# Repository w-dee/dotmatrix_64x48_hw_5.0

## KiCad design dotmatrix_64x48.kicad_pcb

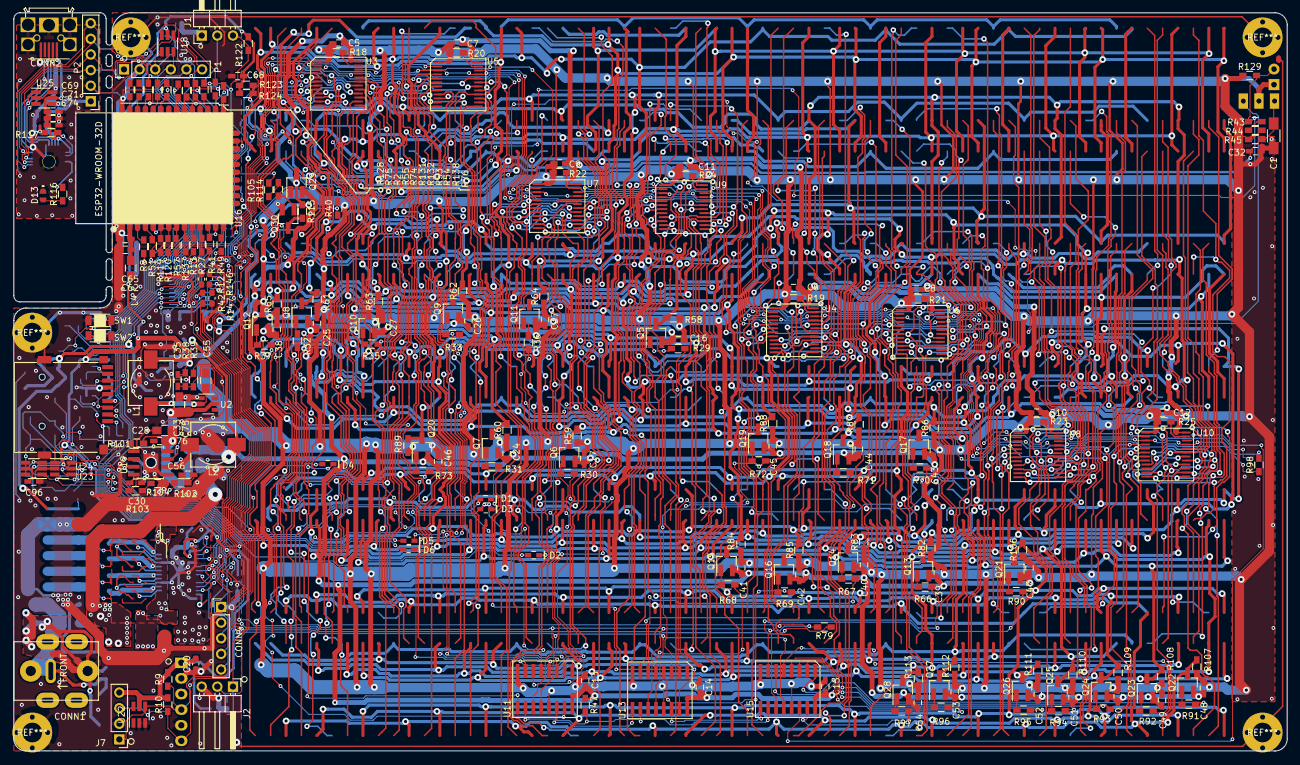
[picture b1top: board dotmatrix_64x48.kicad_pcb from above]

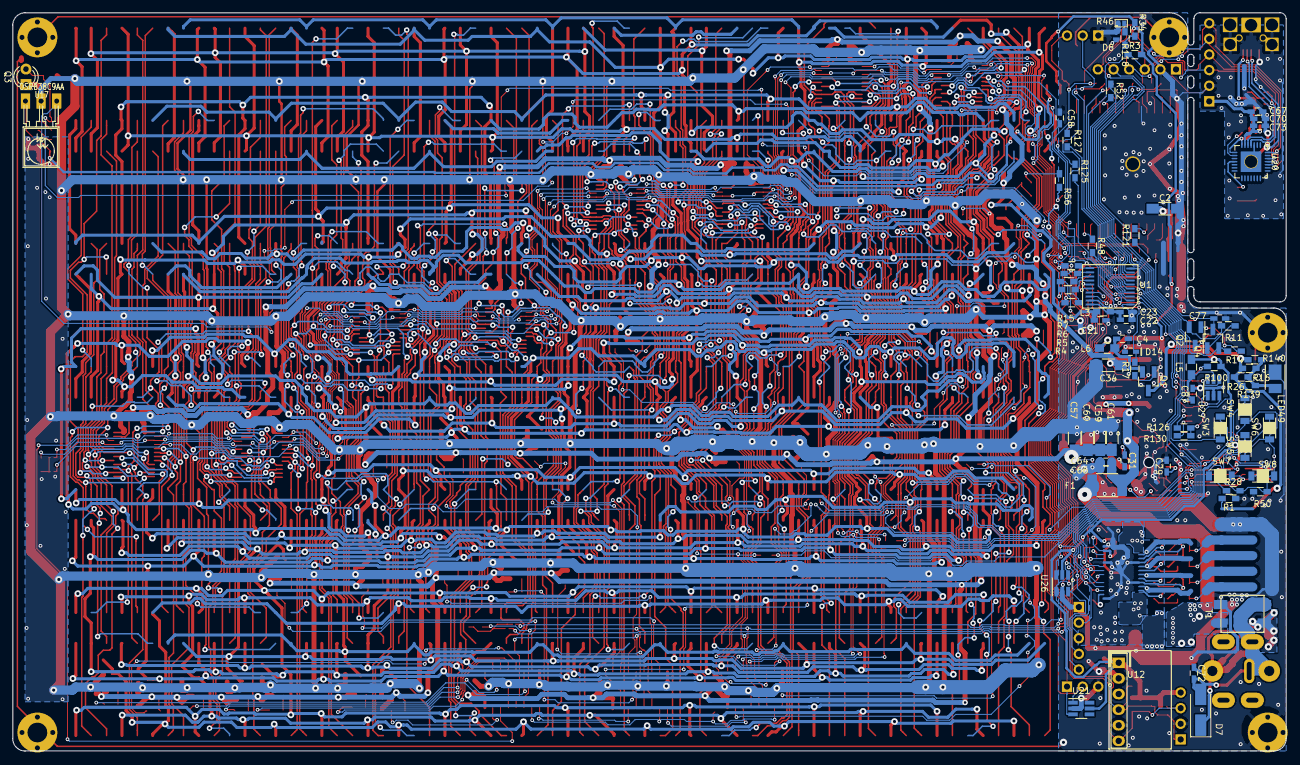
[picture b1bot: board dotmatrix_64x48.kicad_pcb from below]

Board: 2 copper layers, 207.0 x 120.0 mm, 307 parts (77 on the bottom side), 219 nets.

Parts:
C1, C2, C34, C57, C59, C60, C61: 10u; C_1206_HandSoldering
C4, C5, C6, C7, C8, C9, C10, C11, C12, C13, C14, C15, C16, C17, C22, C24, C25, C26, C27, C29, C32, C37, C38, C39, C40, C41, C42, C43, C44, C45, C46, C47, C48, C49, C50, C51, C52, C53, C54, C62, C64, C68, C70, C71, C87, C96: 1u; C_0603_HandSoldering
C20: 1u; C_0603_1608Metric_Pad1.05x0.95mm_HandSolder
C21, C23, C30, C31, C65, C66, C72, C73, C74, C77: 0.1u; C_0603_HandSoldering
C28, C33: 10u 16V; C_0805_HandSoldering
C35, C56: 22p; C_0603_HandSoldering
C55: 0.1u; C_0805_HandSoldering
C58: 0.1u DNI; C_0603_HandSoldering
C67, C69: 10u; C_0603_HandSoldering
C75, C76: 1u 16V; C_0603_HandSoldering
CONN1: BARREL_JACK; BARREL_JACK_HIGH_CURRENT_PJ018
CONN2: USB_OTG; USB-MICRO-B-RECEPT-UNIVERSAL
CONN4: Pin_Header_Straight_1x05_Pitch2.54mm
D1, D2, D3, D4, D5, D6, D14: D_Schottky_Small; SOD-523-mod
D7: 12V TVS diode; D_SMA_Handsoldering
D8, D13: Led_Small; LED1608_Handsoldering
F1: FUSE; R_1812
J1: Conn_01x03_Female; Pin_Header_Angled_1x03_Pitch2.54mm
J2: Conn_01x03_Male; Pin_Header_Angled_1x03_Pitch2.54mm
J3: Micro_SD_Card; microSD_Push_Push_SMD
J7: Conn_01x04_Female; Pin_Header_Straight_1x04_Pitch2.54mm
L1: 10uH; Choke_SMD_7.3x7.3_H3.5_handsoldering
L2: 2.2uH; Choke_SMD_7.3x7.3_H3.5_handsoldering
L3: BLM18RK102SN1 1k @ 100MHz; R_0603_HandSoldering
L4, L5, L6: BLM21PG331SN 300R@100MHz; C_0805_HandSoldering
LED49: IR; LED_PLCC_2835_Handsoldering
P1, P2: CONN_01X06; Pin_Header_Straight_1x06_Pitch2.54mm
Q1, Q5, Q6, Q7, Q8, Q9, Q10, Q11, Q12, Q13, Q14, Q15, Q16, Q17, Q18, Q19, Q20, Q21, Q22, Q23, Q24, Q25, Q26, Q27, Q28, Q29: AO3401; SOT-23_Handsoldering
Q2, Q4, Q30: Q_NPN_BEC; SOT-23_Handsoldering
Q3: NJL7302L-F3; LED_D3.0mm
R1, R9, R10, R47, R58, R59, R60, R61, R62, R63, R64, R65, R82, R83, R84, R85, R86, R87, R88, R89, R106, R107, R108, R109, R110, R111, R112, R113, R114, R138: 4.7k; R_0603_HandSoldering
R2, R5, R16, R17, R26, R29, R30, R31, R32, R33, R35, R36, R37, R66, R67, R68, R69, R70, R71, R72, R73, R74, R75, R90, R91, R92, R93, R94, R95, R96, R97, R105, R115, R139, R140: 10R; R_0603_HandSoldering
R3, R11, R14, R28, R43, R44, R45, R100, R101, R104, R118, R122, R126, R129, R130: 10k; R_0603_HandSoldering
R4, R6, R7, R8, R13, R15, R27, R41, R48, R49, R51, R52, R53, R54, R55, R56, R57, R76, R119, R120, R121, R123, R124, R125, R127, R128, R131, R132, R137: 120R; R_0603_HandSoldering
R12, R42, R146, R147: 10R; R_0603_1608Metric_Pad1.05x0.95mm_HandSolder
R18, R19, R20, R21, R22, R23, R24, R25, R39, R40, R103: 22k; R_0603_HandSoldering
R34, R38, R102: 100k; R_0603_HandSoldering
R46: 0; SolderJumper_S
R50: 10k DNI; R_0603_HandSoldering
R77, R78, R80, R81, R133, R134, R135, R136: 0; J_0.16mm
R79, R98, R116, R117: 1k; R_0603_HandSoldering
SW1, SW2, SW3, SW4, SW5, SW6, SW7, SW8: SW_PUSH_SMALL_H; TACT_SW_SMD_Panasonic-EVPAWBD2A
T1: COMMON_MODE_CHOKE; Choke_COMMON_SMD_ACM7060
U1: 74VHC541; SOIC-20-0.65mm-w8.0mm
U2: TPS54202; SOT-23-6
U3, U4, U5, U6, U7, U8, U9, U10: LED1642GW; SOIC-24-0.65mm-w8.0mm
U11, U13, U15: 74HC595; SOIC-16-1.27mm
U12: AE-BME280
U16: ESP32-WROOM
U17: OSRB38C9AA; IRM2161_LAY
U18, U21, U22, U23, U24, U25, U26, U27: CM1293A-04SO; SOT-23-6_Handsoldering
U19: TPS54428DDA; TI_SO-PowerPAD-8
U20: CP2102N-A01-GQFN28; QFN-28-1EP_5x5mm_Pitch0.5mm-handsoldering

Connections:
/CC_GUARD0: R80.2, R135.1
/CC_GUARD1: R81.2, R136.1
/HC541VDD: C22.1, C23.1, L3.2, U1.20
/IR_Sensor/FILT_VDD: C1.1, C32.1, R45.2, R123.1, R124.1, U17.3
/RC_GUARD0: R77.2, R133.1
/RC_GUARD1: R78.2, R134.1
/SD_VDD: C87.1, J3.4, L5.2, U27.5
/USB_UART/USB3V3: C67.1, C70.1, C73.1, P2.1, R117.2, U20.6
/USB_UART/USBDN: CONN2.2, U20.5, U25.3
/USB_UART/USBDP: CONN2.3, U20.4, U25.1
/USB_UART/VBUS: C69.1, C71.1, C74.1, CONN2.1, U20.7, U20.8, U25.5
/power/DC_IN_N: C72.2, CONN1.2, CONN1.3, D7.2, T1.2
/power/LEDDC_SW: C31.2, L2.2, U19.6
/row_driver/IN0: R66.2, U13.7
/row_driver/IN0_1: R90.2, U15.7
/row_driver/IN1: R91.2, U15.6
/row_driver/IN1_1: R67.2, U13.6
/row_driver/IN2: R92.2, U15.5
/row_driver/IN2_1: R68.2, U13.5
/row_driver/IN3: R93.2, U15.4
/row_driver/IN3_1: R69.2, U13.4
/row_driver/IN4: R94.2, U15.3
/row_driver/IN4_1: R70.2, U13.3
/row_driver/IN5: R95.2, U15.2
/row_driver/IN5_1: R71.2, U13.2
/row_driver/IN6: R96.2, U15.1
/row_driver/IN6_1: R36.2, U11.1
/row_driver/IN6_2: R72.2, U13.1
/row_driver/IN7: R37.2, U11.15
/row_driver/IN7_1: R97.2, U15.15
/row_driver/IN7_2: R73.2, U13.15
/row_driver/SEL1: D1.1, R29.2, U11.7
/row_driver/SEL2: D2.1, R30.2, U11.6
/row_driver/SEL3: D3.1, R31.2, U11.5
/row_driver/SEL4: D4.1, R32.2, U11.4
/row_driver/SEL5: D5.1, R33.2, U11.3
/row_driver/SEL6: D6.1, R35.2, U11.2
/row_driver/SWPAD_CANCEL: D6.2, SW8.1, U24.3
/row_driver/SWPAD_DOWN: D3.2, SW5.1, U23.4
/row_driver/SWPAD_LEFT: D1.2, SW3.1, U23.1
/row_driver/SWPAD_OK: D5.2, SW7.1, U24.1
/row_driver/SWPAD_RIGHT: D4.2, SW6.1, U23.6
/row_driver/SWPAD_UP: D2.2, SW4.1, U23.3
BUTTONSENSE: R28.2, R50.1, R120.2, SW3.2, SW4.2, SW5.2, SW6.2, SW7.2, SW8.2, U24.4
COLCLK: R4.2, R98.2, U3.3, U3.21, U4.3, U4.21, U5.3, U5.21, U6.3, U6.21, U7.3, U7.21, U8.3, U8.21, U9.3, U9.21, U10.3, U10.21
COLLATCH: R5.2, U3.4, U4.4, U5.4, U6.4, U7.4, U8.4, U9.4, U10.4
COLSER: R15.2, U3.2
COLSEROUT: U10.22, U15.14
DC_IN_P: C72.1, CONN1.1, D7.1, T1.1
DTR: P1.5, P2.5, Q4.2, R11.2, U18.4, U20.28
D_COLCLK: R131.2, U1.9
D_COLLATCH: R52.1, U1.8
D_COLSER: R132.2, U1.6
D_I2S_SPK_BCLK: R13.2, U1.4
D_I2S_SPK_DATA: R41.2, U1.2
D_I2S_SPK_LRCLK: R27.2, U1.3
D_I2S_SPK_MCLK: R137.2, U1.5
D_LED1642_RST: R56.1, R105.1
D_ROW_LAT: R34.1, R57.1, R118.1, U1.7
ESPVDD: C2.1, C62.1, C65.1, L4.2, U16.2
E_AIN: C58.1, Q3.2, R43.1, R121.1, R129.2
E_EN: C77.2, Q2.3, R8.1, SW1.1
E_GPIO0: Q4.3, R76.1, SW2.2
E_HS2_CLK: J3.5, R48.2, U27.3
E_HS2_CMD: J3.3, R125.1, U27.1
E_HS2_DATA0: J3.7, R127.1, U27.4
E_RX: P1.3, P2.3, R3.1, R55.1, U18.1, U20.26
E_RX2: J1.3, J2.2, R54.2, R122.1, U21.1
E_TX: P1.4, P2.4, R2.1, U18.3, U20.25
E_TX2: J1.2, J2.1, R53.2, U21.3
GND: C1.2, C2.2, C4.2, C5.2, C6.2, C7.2, C8.2, C9.2, C10.2, C11.2, C12.2, C13.2, C14.2, C15.2, C16.2, C17.2, C20.1, C21.2, C22.2, C23.2, C24.2, C25.2, C26.2, C27.2, C28.2, C29.2, C30.2, C32.2, C33.2, C34.2, C37.2, C38.2, C39.2, C40.2, C41.2, C42.2, C43.2, C44.2, C45.2, C46.2, C47.2, C48.2, C49.2, C50.2, C51.2, C52.2, C53.2, C54.2, C57.2, C58.2, C59.2, C60.2, C61.2, C62.2, C64.2, C65.2, C66.2, C67.2, C68.2, C69.2, C70.2, C71.2, C73.2, C74.2, C75.2, C76.2, C77.1, C87.2, C96.2, CONN2.5, CONN2.6, CONN4.1, D8.1, D13.1, D14.2, J1.1, J2.3, J3.6, J3.9, J7.2, LED49.1, P1.2, P2.2, Q3.1, Q30.2, R1.1, R18.2, R19.2, R20.2, R21.2, R22.2, R23.2, R24.2, R25.2, R39.1, R46.2, R50.2, R58.1, R59.1, R60.1, R61.1, R62.1, R63.1, R64.1, R65.1, R77.1, R78.1, R80.1, R81.1, R82.1, R83.1, R84.1, R85.1, R86.1, R87.1, R88.1, R89.1, R104.1, R106.1, R107.1, R108.1, R109.1, R110.1, R111.1, R112.1, R113.1, R129.1, SW1.2, SW2.1, T1.3, U1.1, U1.10, U1.19, U2.1, U3.1, U4.1, U5.1, U6.1, U7.1, U8.1, U9.1, U10.1, U11.8, U11.13, U12.2, U12.5, U13.8, U13.13, U15.8, U15.13, U16.1, U16.15, U16.38, U16.39, U17.2, U18.2, U19.5, U19.9, U20.3, U20.29, U21.2, U22.2, U22.3, U23.2, U24.2, U25.2, U25.4, U25.6, U26.2, U27.2
HC595CLK: R6.2, R79.2, U11.11, U13.11, U15.11
HC595LATCH: R7.2, U11.12, U13.12, U15.12
HC595SEROUT: R119.2, U11.9
I2S_SPK_BCLK: CONN4.4, R42.2, U26.3
I2S_SPK_DATA: CONN4.2, R147.2, U26.6
I2S_SPK_LRCLK: CONN4.3, R146.2, U26.4
I2S_SPK_MCLK: CONN4.5, R12.2, U26.1
IRLED_A: Q1.3, R1.2, R16.2, R26.2, R139.2, R140.2
IR_IN: R40.2, R51.1, U17.1
IR_OUT: D14.1, R17.2, R49.2
LED1642VDD: C5.1, C6.1, C7.1, C8.1, C9.1, C10.1, C11.1, C12.1, C21.1, L3.1, Q29.3, R115.1, U3.24, U4.24, U5.24, U6.24, U7.24, U8.24, U9.24, U10.24
LEDLOGICVDD: C20.2, C34.1, C35.1, C68.1, C96.1, J7.4, L1.1, L4.1, L5.1, Q29.2, R3.2, R9.2, R10.2, R28.1, R34.2, R38.2, R40.1, R100.2, R122.2, R123.2, R124.2, R126.2, R130.2, U12.1, U18.5, U21.5, U22.5, U23.5, U24.5, U26.5
LEDVDD: C13.1, C14.1, C15.1, C16.1, C17.1, C24.1, C25.1, C26.1, C27.1, C37.1, C38.1, C39.1, C40.1, C41.1, C42.1, C43.1, C44.1, C45.1, C46.1, C47.1, C48.1, C49.1, C50.1, C51.1, C52.1, C53.1, C54.1, C56.1, C57.1, C59.1, C60.1, C61.1, L2.1, L6.1, Q5.2, Q6.2, Q7.2, Q8.2, Q9.2, Q10.2, Q11.2, Q12.2, Q13.2, Q14.2, Q15.2, Q16.2, Q17.2, Q18.2, Q19.2, Q20.2, Q21.2, Q22.2, Q23.2, Q24.2, Q25.2, Q26.2, Q27.2, Q28.2, R47.1, R102.2, U11.16, U13.16, U15.16
MS_SEL: R46.1, R118.2
unnamed: C4.1, L6.2, Q1.2
unnamed: C29.1, U19.3
unnamed: C30.1, U19.4
unnamed: C31.1, U19.7
unnamed: C35.2, R38.1, R39.2, U2.4
unnamed: C55.1, U2.6
unnamed: C55.2, L1.2, U2.2
unnamed: C56.2, R102.1, R103.2, U19.2
unnamed: D8.2, R138.2
unnamed: D13.2, R116.1
unnamed: J3.1, R130.1
unnamed: J3.2, R126.1
unnamed: J3.8, R100.1
unnamed: LED49.2, R16.1, R26.1, R139.1, R140.1
unnamed: Q1.1, R17.1
unnamed: Q2.1, R11.1
unnamed: Q4.1, R14.1
unnamed: Q5.1, R29.1
unnamed: Q6.1, R30.1
unnamed: Q7.1, R31.1
unnamed: Q8.1, R32.1
unnamed: Q9.1, R33.1
unnamed: Q10.1, R35.1
unnamed: Q11.1, R36.1
unnamed: Q12.1, R37.1
unnamed: Q13.1, R66.1
unnamed: Q14.1, R67.1
unnamed: Q15.1, R68.1
unnamed: Q16.1, R69.1
unnamed: Q17.1, R70.1
unnamed: Q18.1, R71.1
unnamed: Q19.1, R72.1
unnamed: Q20.1, R73.1
unnamed: Q21.1, R90.1
unnamed: Q22.1, R91.1
unnamed: Q23.1, R92.1
unnamed: Q24.1, R93.1
unnamed: Q25.1, R94.1
unnamed: Q26.1, R95.1
unnamed: Q27.1, R96.1
unnamed: Q28.1, R97.1
unnamed: Q29.1, R105.2, R114.1
unnamed: Q30.1, R114.2
unnamed: Q30.3, R115.2
unnamed: R2.2, U16.35
unnamed: R4.1, R6.1, U1.13
unnamed: R5.1, U1.14
unnamed: R7.1, U1.12
unnamed: R8.2, U16.3
unnamed: R12.1, U1.18
unnamed: R13.1, U16.10
unnamed: R15.1, U1.11
unnamed: R18.1, U3.23
unnamed: R19.1, U4.23
unnamed: R20.1, U5.23
unnamed: R21.1, U6.23
unnamed: R22.1, U7.23
unnamed: R23.1, U8.23
unnamed: R24.1, U9.23
unnamed: R25.1, U10.23
unnamed: R27.1, U16.11
unnamed: R41.1, U16.12
unnamed: R42.1, U1.17
unnamed: R43.2, R44.1
unnamed: R44.2, R45.1
unnamed: R47.2, U11.10, U13.10, U15.10
unnamed: R48.1, U16.13
unnamed: R49.1, U16.14
unnamed: R51.2, U16.4
unnamed: R52.2, U16.29
unnamed: R53.1, U16.28
unnamed: R54.1, U16.27
unnamed: R55.2, U16.34
unnamed: R56.2, U16.16
unnamed: R57.2, U16.8
unnamed: R74.2, U16.33
unnamed: R75.2, U16.36
unnamed: R76.2, U16.25
unnamed: R101.1, U19.1
unnamed: R103.1, R104.2
unnamed: R116.2, U20.11
unnamed: R117.1, U20.9
unnamed: R119.1, U16.6
unnamed: R120.1, U16.7
unnamed: R121.2, U16.5
unnamed: R125.2, U16.23
unnamed: R127.2, U16.24
unnamed: R128.2, U16.37
unnamed: R131.1, U16.31
unnamed: R132.1, U16.30
unnamed: R79.1, R133.2, R134.2
unnamed: R98.1, R135.2, R136.2
unnamed: R137.1, U16.9
unnamed: R138.1, U16.26
unnamed: R146.1, U1.16
unnamed: R147.1, U1.15
unnamed: U3.22, U5.2
unnamed: U4.2, U9.22
unnamed: U4.22, U6.2
unnamed: U5.22, U7.2
unnamed: U6.22, U8.2
unnamed: U7.22, U9.2
unnamed: U8.22, U10.2
unnamed: U11.14, U13.9
unnamed: U13.14, U15.9
RTS: P1.6, P2.6, Q2.2, R14.2, U18.6, U20.24
SCL: J7.3, R10.1, R75.1, U12.6, U22.6
SDA: J7.1, R9.1, R74.1, U12.4, U22.4
V12_PREFUSE: F1.1, T1.4
VCC: C28.1, C33.1, C64.1, C66.1, C75.1, C76.1, F1.2, R101.2, U2.3, U2.5, U19.8
r0: Q5.3, R58.2
r1: Q6.3, R59.2
r2: Q7.3, R60.2
r3: Q8.3, R61.2
r4: Q9.3, R62.2
r5: Q10.3, R63.2
r6: Q11.3, R64.2
r7: Q12.3, R65.2
r8: Q13.3, R82.2
r9: Q14.3, R83.2
r10: Q15.3, R84.2
r11: Q16.3, R85.2
r12: Q17.3, R86.2
r13: Q18.3, R87.2
r14: Q19.3, R88.2
r15: Q20.3, R89.2
r16: Q21.3, R106.2
r17: Q22.3, R107.2
r18: Q23.3, R108.2
r19: Q24.3, R109.2
r20: Q25.3, R110.2
r21: Q26.3, R111.2
r22: Q27.3, R112.2
r23: Q28.3, R113.2

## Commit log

2017-09-12 Modified to use matrix LEDs; Components layout has almost done, tracks and traces not yet.
2017-09-16 Layout almost complete.
2017-09-16 Silk fix; Pattern pull out from ICs fiexed; Vias on pads fixed
2017-09-17 Set away thermelly active components from sensors; Silks and DRC not yet done
2017-09-17 Improved GND impedance
2017-09-17 Added serial pull-ups; DRC clear; Silks should be clear.
2017-09-18 Layout adj. DRC clear
2017-09-19 Layout improvements; DRC clear
2017-09-24 Fixed LED matrix module's orientation; DRC clear
2017-09-24 Impedance improvements; DRC clear
2017-09-25 Removed termination resisters (was never used in 3.0 series); Pattern improvements; DRC clear
2017-09-26 Small fixes; DRC clear
2017-10-02 DRC clear; This project likely to be abandoned due to 4MiB Flash version WROOM-02 shortage.
2017-10-13 This is the MazoClock hw 4.0 series; Uses ESP32 processor instead of ESP8266 used in prior MazoClock hw 3.0 series.
2017-10-14 Fixed button position; DRC clear
2017-10-16 Added some DC-DC convertes; DRC clear
2017-10-22 Added quick-and-dirty class-D amplifier circuit for just testing
2018-09-25 Updated to kicad 6.0.0 rc; removed outdated gerber files; Schematic is not complete
2018-10-17 To ignore cache files
2018-10-17 Heavily modifying; Matrix nets under construction
2018-10-18 Getting very mojai
2018-10-27 Almost all components has placed.
2018-11-05 Too less PCB space.
2018-11-09 Added stereo power amplifier
2018-11-14 Switched to new kicad libraries
2018-11-20 Layout fixup
2018-11-24 Refdeses fixup; There is bunch of Courtyard crossing; I'm going to ignore them. Anyway this board is only for handsoldering.
2018-12-01 Layout fixes
2019-10-07 Version 4.0 commit
2019-10-08 Prior to merge production-1.0's led matrix pattern
2019-10-08 Merged production-1.0's LED matrix onto current design.
2019-10-16 Before removing old style stitching vias
2019-10-23 Design update
2019-10-31 Almost done drawing pcb tracks
2019-11-01 DRC complete. MK5
2019-11-01 Improved stiffness against DC conn's strain / DRC OK
2019-11-02 Prototype gerber out done
2019-11-02 Fixed silk ref dislocation
2019-11-03 Prototype gerber out done, retaken
2019-11-10 Added power input filter circut; Adjust MLCC size/value to be able to use cheap components
2019-11-11 Changed footprints from old 4.x's R/C to 5.x's
2019-11-11 Re-arranged schematic texts not to overlap each other
2019-11-11 AW refine
2019-11-11 Moved SD-related resistors to near ESP32
2019-11-12 Removed led address text and aruco markers; Added scale label instead
2019-11-12 Added via on pads of SMD connector not to easily be detatched from base FR-4
2019-11-15 DRC clear
2019-11-18 Track refining
2019-11-21 Added external IR remote-controller connector; DRC clear
2019-11-25 Relocated buttons to more easily accessible position
2019-11-25 Specified 3V3 LDO as ON semi NCP1117 because its document shows stable MLCC output capacitor capcity/ESR range
2019-11-26 Changed HC595's vdd from LEDVDD to LEDLOGICVDD; Fixed silk refdes'; DRC clean ?(unchecked)
2019-11-27 Fixed USB micro-b's mount polarity; Improved SOT-23-6 1-pin silk marker readability
2019-12-02 LEDVDD now can be up to 5.0V for blue/white LEDs; DRC clear
2019-12-02 Layout cleanup; DRC clear
2019-12-02 Wrote note about making LEDVDD > 4.5V
2019-12-04 Changed I2S ESD diode's returning VDD from LED1642VDD to LEDLOGICVDD
2019-12-04 Fixed IR LED drive voltage range
2020-01-02 Fixed WROOM-32D footprinco; NO DRC CHECKED
2020-01-03 Improved LDO heat dissipation; Button and its diodes rearranged
2020-01-03 Improved pattern design; DRC clear
2020-01-06 Added 4-pin USB pin header connector in case of getting crazy of USB micro-B comming off
2020-01-06 Improved power impedance
2020-01-07 Improved USB micro-b connector strength
2020-01-12 Improved DC jack fixment; DRC clear
2020-01-15 Improved mechanical strength
2020-01-15 Improved thermal dissipation around DC-DC converters
2020-06-30 Improved DCDC output loop
2020-06-30 Schematics format change due to KiCAD's verup
2020-06-30 Removed old format files
2020-07-06 due to file name extension change
2020-07-06 Button component change and removed some ESD diodes
2020-07-07 small modification for ESD handling
2020-07-07 GND impedance improvement
2020-07-10 EMI improvements
2020-07-11 Added a schematic PDF
2020-07-11 Added C80 / removed orphan GND in the schematics
2020-07-11 Swapped Q31 E/C / DRC clear
2020-07-13 Renamed Master/Slave to 責め/受け due to trend of avoidance of discriminative words
2020-07-13 Updated schematic PDF
2020-08-17 Added C before LDO / DRC clear
2020-08-17 Updated the schematic
2020-08-17 Minor changes
2020-08-18 Impedance improvements
2020-08-19 Improved impedance
2020-08-21 WROOM32 coupling capacitor order fixed; Added FB on long line to board left-most sensors
2020-08-24 Changed from USB micro-B to Type C. DRC should be clear.
2020-08-26 Switched to kicad-nightly (not legacy) official repository
2020-08-26 Fixed ring thickness; Fixed WROOM-32D EP position
2020-08-27 Fixed bypass capacitor positions; DRC clear
2020-08-28 Added an external pull-up resistor on GPIO0
2020-08-31 Added IR led protection
2020-09-01 LEDVDD improvments
2020-09-02 Small Improvements
2020-09-02 Added IR transmit status 'visible' indicator
2020-09-07 IR signal line noise reduction
2020-09-07 Added some comments
2020-09-07 Updated schematics PDF
2020-09-08 Trivial fix
2020-09-08 Fixed some comments; Added FB on SCL/SDA line
2020-09-09 Updated the PCB; DRC clear
2020-09-17 Re-arranged physical buttions; DRC clear
2020-09-18 Fixed mirrored 'OK' symbol
2020-09-20 Use BAT54A instead of discrete Ds; DRC NOT clear
2020-09-20 PDF update
2020-09-21 Completed Board Fix; DRC should be OK ...
2020-09-21 Changed 5.05V buck regulator output to 4.65V (to decrease 3.3V LDO heat)
2020-09-21 Schematics update
2020-09-21 Designated photodiode's lead long/short
2020-09-22 DRC clear except for non critical erorrs
2020-09-22 Removed LDO's output copper area under DCDC output inductor (DRC nonchecked
2020-09-23 Added J8.4; DRC clear
2020-09-23 Added some ferrite beads on sensitive lines
2020-09-24 Removed SCL/SDA FBs
2020-09-24 Moved leftside sensors to rightside; Unified old footprints to new footprints; DRC clear
2020-09-26 Changed LDO to one which has more lower drop voltage; DRC clear
2020-09-26 Updated the PDF
2020-09-26 Fixed a comment mismatch; Why KiCAD changes more files than I edited ...
2020-10-09 To use WS2812-2020 as status LEDs; No critical DRC errors found
2020-10-12 Traces fix; DRC may clear
2020-10-16 Pattern fix; DRC might be clear
2020-11-17 Routing adjustments; DRC should be ok
2020-11-18 Changed environment light sensor position; DRC clear
2020-11-30 Gerber out
2021-01-13 Added a schematic comments; I don't know why other files are updated
2021-01-28 Changed L2 value from 2.2uH to '2.2 ~ 6.8uH'
2021-02-01 Settled L2 value to 6.8uH
2021-02-12 Modified BAT54A -> BAT54AT
2021-02-16 Revert "Modified BAT54A -> BAT54AT"
    This reverts commit bff826c2a0df659e4b46f46fdcd99af7f60e1fdb.
2021-02-26 Toward Production rev. 1.0
2021-03-10 Relocated LED's AK notation
2021-03-22 Improved GND impedance a bit; courtyard overlap fix
2021-03-23 Fixed twisted resistor positioning
2021-03-23 Routing improvements
2021-03-26 Reverted L2 value from '6.8u' to '2.2u'. Instead, L7 has changed its value from '2.2u' to '6.8u' to preserve total component BOM. The reason is sound noise from L2.
2021-04-05 Experimental modification for audible noise redution at DC-DC converters
2021-04-05 Fixed silk positions
2021-04-06 Improved placements
2021-04-06 Improved routes
2021-04-07 Improved routing
2021-04-07 Enbold GND patterns
2021-04-09 Improved routings
2021-04-13 Improved SD card VDD line
2021-04-14 Improved audible noize reduction; DRC clear
2021-04-14 Routes cleanup; DRC clear
2021-04-15 Moved some components apart from the matrix
2021-04-16 Changed revision mark; improved routes; DRC clear
2021-04-16 Removed PML caps; I concluded they do not help audible noise reduction; DRC clear
2021-04-19 Beta 2 commited
2021-05-04 Reverted L2 value to 6.8uH (Sorry I have bought too many 6.8uH'sgit statusgit status)
2021-07-09 KiCAD ver. up
2021-07-09 Added C94; Moved I2C pull-up Rs to more near MCU
